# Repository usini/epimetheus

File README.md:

# epimetheus
ESP32 Modular Sensor with Web interface - Websocket API / Flash save.

## Connectivité

## Interface Web

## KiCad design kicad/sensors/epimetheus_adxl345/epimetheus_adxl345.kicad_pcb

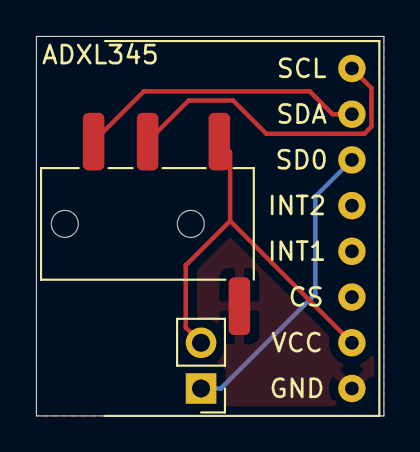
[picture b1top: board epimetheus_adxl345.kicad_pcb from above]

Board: 2 copper layers, 19.3 x 21.1 mm, 3 parts (0 on the bottom side), 5 nets.

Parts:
J1: AudioJack4; jack_3.5mm_TRRS
J2: Jumper Address; PinHeader_1x02_P2.54mm_Vertical
U1: module_adxl345

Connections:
+3V3: J1.T, J2.2, U1.2
GND: J1.S, U1.1
SCL: J1.R1, U1.8
SD0: J2.1, U1.6
SDA: J1.R2, U1.7

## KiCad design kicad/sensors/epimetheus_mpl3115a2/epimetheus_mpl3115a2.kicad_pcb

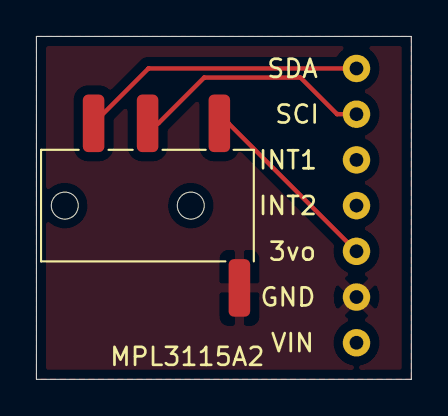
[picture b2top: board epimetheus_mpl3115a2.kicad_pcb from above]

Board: 2 copper layers, 20.8 x 19.1 mm, 3 parts (1 on the bottom side), 4 nets.

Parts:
J1: AudioJack4; jack_3.5mm_TRRS
L1: LOGO; temp_hum_baro_logo
U1: module_mpl3115a2

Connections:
+3V3: J1.T, U1.3
GND: J1.S, U1.2
SCL: J1.R1, U1.6
SDA: J1.R2, U1.7

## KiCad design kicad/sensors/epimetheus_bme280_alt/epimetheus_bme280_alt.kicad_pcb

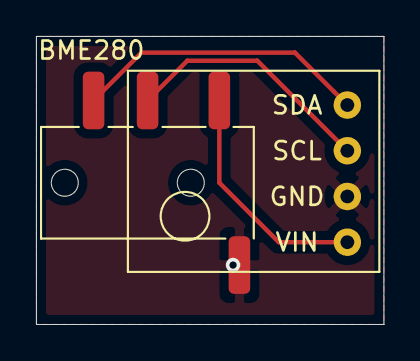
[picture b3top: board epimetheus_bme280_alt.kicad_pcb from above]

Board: 2 copper layers, 19.3 x 16.0 mm, 3 parts (1 on the bottom side), 4 nets.

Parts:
J1: AudioJack4; jack_3.5mm_TRRS
L1: LOGO; temp_hum_baro_logo
U1: module_bme280_alt

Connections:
+3V3: J1.T, U1.1
GND: J1.S, U1.2
SCL: J1.R1, U1.3
SDA: J1.R2, U1.4

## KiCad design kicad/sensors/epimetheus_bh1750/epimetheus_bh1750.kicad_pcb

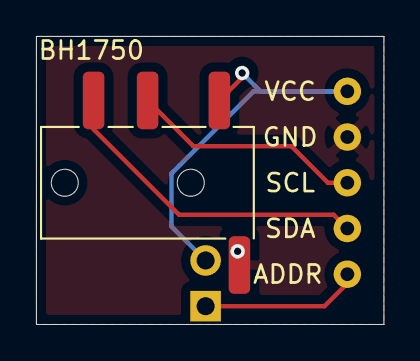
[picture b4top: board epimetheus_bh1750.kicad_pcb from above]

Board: 2 copper layers, 19.3 x 16.0 mm, 3 parts (0 on the bottom side), 5 nets.

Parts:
J1: AudioJack4; jack_3.5mm_TRRS
J2: Jumper Address; PinHeader_1x02_P2.54mm_Vertical
U1: module_bh1750

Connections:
+3V3: J1.T, J2.2, U1.5
ADDR: J2.1, U1.1
GND: J1.S, U1.4
SCL: J1.R1, U1.3
SDA: J1.R2, U1.2

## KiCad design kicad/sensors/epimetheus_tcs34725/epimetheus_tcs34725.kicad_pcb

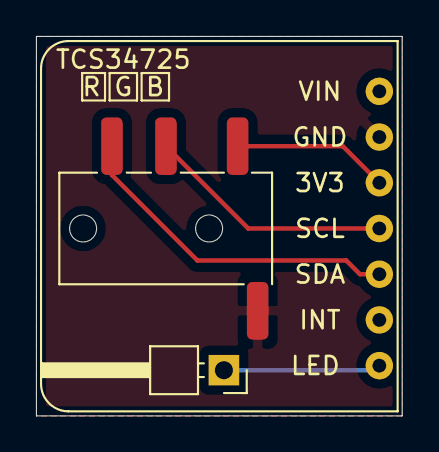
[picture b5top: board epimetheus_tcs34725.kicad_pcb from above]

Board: 2 copper layers, 20.3 x 21.1 mm, 3 parts (0 on the bottom side), 5 nets.

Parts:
J1: AudioJack4; jack_3.5mm_TRRS
J2: LED; PinHeader_1x01_P2.54mm_Horizontal
U1: module_tcs34725

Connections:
+3V3: J1.T, U1.5
GND: J1.S, U1.6
LED: J2.1, U1.1
SCL: J1.R1, U1.4
SDA: J1.R2, U1.3

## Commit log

2020-08-14 Added MQTT
2020-08-14 Fix Wifi hotspot mode
    - WIFI_AP already exists, rename it to WIFI_HOTSPOT
    - Mqtt disconnect if unavailable
2020-08-14 Rename web to network
    Investigating issue with MQTT.
2020-08-19 Add Kicad sensor adaptor
2020-08-19 Add st7789 display
2020-08-19 Add esp32 step file
2020-10-02 Dump v0.2
    As time was of the essence, and I was developing this alone, versioning was not done (shame!)
    This version is more of a dump of all code / some unfinished schematics, and (not always translate) docs
    It should works fine, but it definitely not bug-free as for now.
2020-10-03 Testing github actions (CI)
2020-10-03 Continous Integration
2020-10-03 Add BME280 (not supported)
    BME280 / BME680 has the same i²c address, we need to find a way to differentiate it, as for now it won't get active
    I don't actually have my bme680 sensor to do test so it is going stalled.
2020-10-04 Add BME280 Scan Serial
2020-10-04 Add BME280 support
    BME280 support now works, we check if we can start BME680 and if it failed we try with BME280.
    Not tested with BME680 but should works.
    Rework connection/disconnection as it seems it wasn't working correctly (Sensor was setup at each scan)
2020-10-05 Add BH1750 Light Sensor
    Some correction to BME280 was added, and typo / variables inconsistancy were also corrected.
2020-10-06 Add MAX30102 sensor (heartrate)
    - MAX30102 sensor uses millis() and could not works with others sensors, for time critical sensor maybe use freeRTOS task system ?
    - update sensors is now as safe as possible (could induce errors in others sensors)
    -Minor correction on comments
    -Disable get_clock when DS3231 not present (alternative method should be in place like NTP/Internal RTC)
    - BH1750 in update websocket array was incorrect and cause fatal error
    - Add BPM type of sensor
2020-10-06 Basic Round Robin system for data on web
    As we have a rate of 1 seconds of data, Data array on the web interface rapidly become massive and become hard to read and can be hard on the CPU of the phone/computer
    This is a basic implementation of Round Robin system, where older data get average, not really good for now so not export to the ESP.
2020-10-06 Add LABSud as coauthor of the sensor
2020-10-06 Make MAX30102 less sensitive
    Reject any value inferior to 40bpm and superior to 200.
    Based on https://en.wikipedia.org/wiki/Heart_rate which show that heart rate is unlikely to go as fast or slow than this.
2020-10-06 Add MPU6050
    As MPU6050 first address conflict with DS3231, we first check if this is a MPU6050 sensor and if it failed activate DS3231, note that RTCLib doesn't have a way to really check if DS3231 really begin.
    - I changed the way the clock is manage, as at first it was started on setup() so that it was more clear that the clock was manage.
2020-10-06 Add BMP280 sensor
    Conflict with BME680/BME280, check bme680 if begin then BMP280 and if it doesn't begin go with BME280.
    Seems to works fine.
2020-12-03 SDA_PIN and SCL_PIN was incorrectly set to boolean (instead of int)
2020-12-03 Remove trailing space
2022-02-09 Last version (not checked)
